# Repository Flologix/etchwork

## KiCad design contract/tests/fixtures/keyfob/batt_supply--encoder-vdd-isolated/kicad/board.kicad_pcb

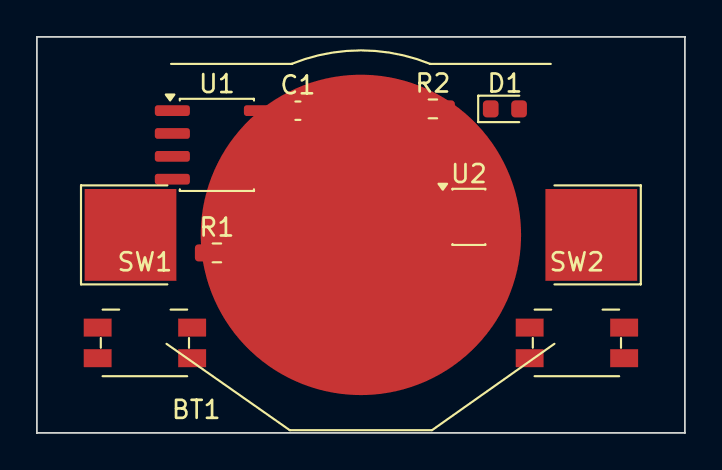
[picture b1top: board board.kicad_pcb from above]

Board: 2 copper layers, 36.0 x 22.0 mm, 9 parts (0 on the bottom side), 8 nets, no tracks yet.

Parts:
BT1: CR2032; BatteryHolder_Keystone_3002_1x2032
C1: 100n; C_0603_1608Metric
D1: RED; LED_0603_1608Metric
R1: 330k; R_0603_1608Metric
R2: 1k; R_0603_1608Metric
SW1, SW2: SW_Push; Panasonic_EVQPUJ_EVQPUA
U1: EV1527; SOIC-8_3.9x4.9mm_P1.27mm
U2: SYN115; SOT-23-6

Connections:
DOUT: R2.1, U1.7 (DOUT), U2.6 (DATA)
GND: BT1.2 (-), C1.2, D1.1 (K), U1.1 (VSS), U2.2 (VSS)
LED_A: D1.2 (A), R2.2
NET3: R1.1, U1.2 (OSC)
N_SW1: SW1.2, U1.3 (K0)
N_SW2: SW2.2, U1.4 (K1)
VCC: BT1.1 (+), R1.2, SW1.1, SW2.1, U2.5 (VDD)
VENC: C1.1, U1.8 (VDD)
